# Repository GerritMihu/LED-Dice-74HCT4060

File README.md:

# LED-Dice-74HCT4060

 LED Spielwürfel (Dice) mit dem 14-Bit Zähler 74HCT4060

## Funktionsbeschreibung

 * Der Würfel zeigt beim Drücken des Tasters die Zahlen von 1-6 an.
 * Solange der Taster SW1 nicht gedrückt ist leuchten alle LED's

## Arbeitsauftrag

- [ ] Kommissionieren Sie alle Bauteile
- [ ] Fertigen Sie die Leiterplatte
- [ ] Prüfen Sie jedes Bauteil auf Löt- & Bestückfehler
- [ ] Prüfen Sie die Leiterplatte auf Kurzschlüss in der Versorgung
- [ ] Nehmen Sie die Leiterplatte mit 5V Versorgung in Betrieb
- [ ] Berechnen Sie die Frequenz des Oszillators mithlife des Datenblattes von IC1
- [ ] Erstellen Sie eine Wahrheitstabelle für die erweiterte Funktionsbeschreibung
- [ ] Dokumentieren Sie Ihre Arbeit

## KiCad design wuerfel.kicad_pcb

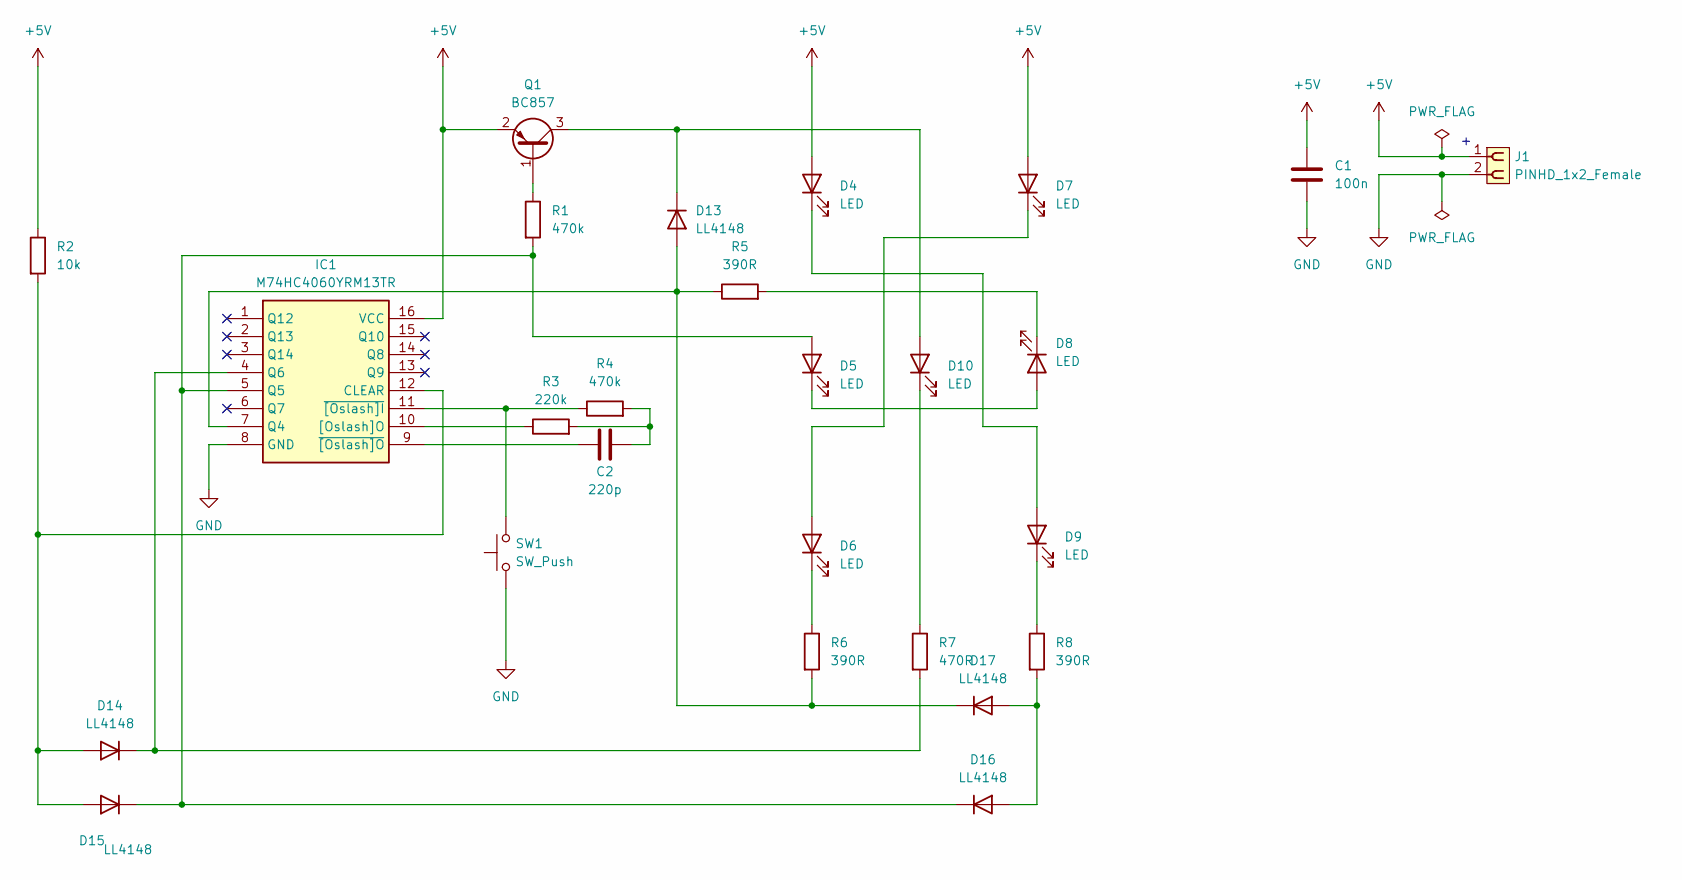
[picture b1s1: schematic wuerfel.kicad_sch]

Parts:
C1: 100n; C_0805_2012Metric_Pad1.18x1.45mm_HandSolder
C2: 220p; C_0805_2012Metric_Pad1.18x1.45mm_HandSolder
D4, D5, D6, D7, D8, D9, D10: LED; LED_0805_2012Metric_Pad1.15x1.40mm_HandSolder
D13, D14, D15, D16, D17: LL4148; D_MiniMELF
IC1: M74HC4060YRM13TR; SOIC-16_3.9x9.9mm_P1.27mm; Manufacturer_Part_Number M74HC4060YRM13TR; Mouser Part Number 511-M74HC4060YRM13TR
J1: PINHD_1x2_Female; PinSocket_1x02_P2.54mm_Vertical
Q1: BC857; SOT-23
R1, R4: 470k; R_1206_3216Metric_Pad1.30x1.75mm_HandSolder
R2: 10k; R_1206_3216Metric_Pad1.30x1.75mm_HandSolder
R3: 220k; R_1206_3216Metric_Pad1.30x1.75mm_HandSolder
R5, R6, R8: 390R; R_1206_3216Metric_Pad1.30x1.75mm_HandSolder
R7: 470R; R_1206_3216Metric_Pad1.30x1.75mm_HandSolder
SW1: SW_Push; SW_Push_1P1T_NO_CK_KSC6xxJ

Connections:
+5V: C1.1, D4.2 (A), D7.2 (A), IC1.16 (VCC), J1.1, Q1.2 (E), R2.1
GND: C1.2, IC1.8 (GND), J1.2, SW1.1
unnamed: C2.2, R3.2, R4.2
unnamed: D4.1 (K), D9.2 (A)
unnamed: D5.1 (K), D8.2 (A)
unnamed: D6.2 (A), D7.1 (K)
unnamed: D6.1 (K), R6.1
unnamed: D8.1 (K), R5.2
unnamed: D9.1 (K), R8.1
unnamed: D10.2 (A), D13.1 (K), Q1.3 (C)
unnamed: D10.1 (K), R7.1
unnamed: D13.2 (A), D17.1 (K), IC1.7 (Q4), R5.1, R6.2
unnamed: D14.2 (A), D15.2 (A), IC1.12 (CLEAR), R2.2
unnamed: D14.1 (K), IC1.4 (Q6), R7.2
unnamed: D5.2 (A), D15.1 (K), D16.1 (K), IC1.5 (Q5), R1.2
unnamed: D16.2 (A), D17.2 (A), R8.2
unnamed: IC1.10 ([Oslash]O), R3.1
unnamed: IC1.11 (~[Oslash]I), R4.1, SW1.2
unnamed: C2.1, IC1.9 (~[Oslash]O)
unnamed: Q1.1 (B), R1.1

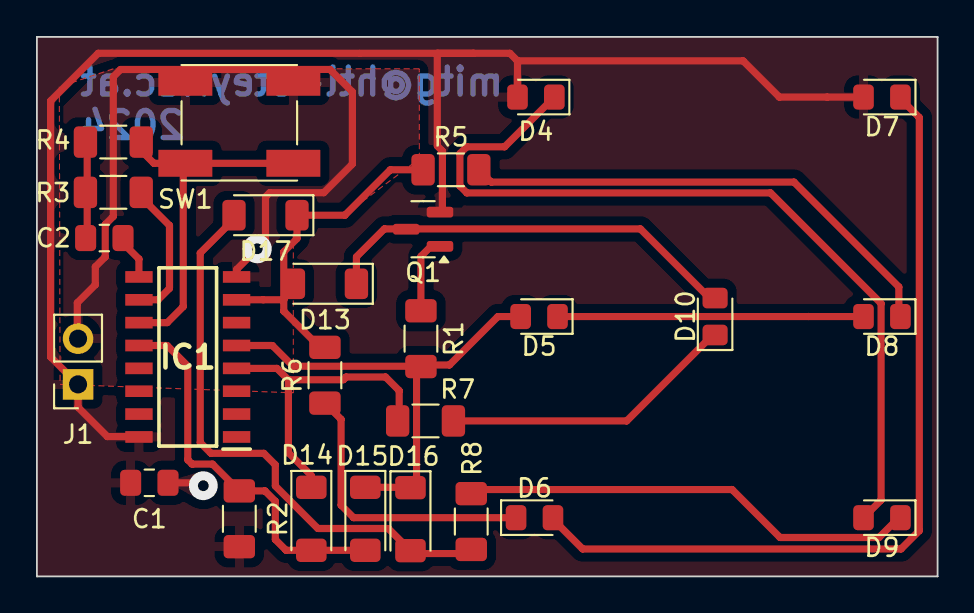
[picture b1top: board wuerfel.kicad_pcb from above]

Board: 2 copper layers, 50.0 x 30.0 mm, 26 parts (0 on the bottom side), 20 nets.

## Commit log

2024-04-22 Updated PCBA for production
2024-04-22 Generated Gerber updated Readme
2024-04-22 README.md aktualisieren
2024-04-23 Error at groundplane sw1
2024-05-02 cleanup add folder pics
